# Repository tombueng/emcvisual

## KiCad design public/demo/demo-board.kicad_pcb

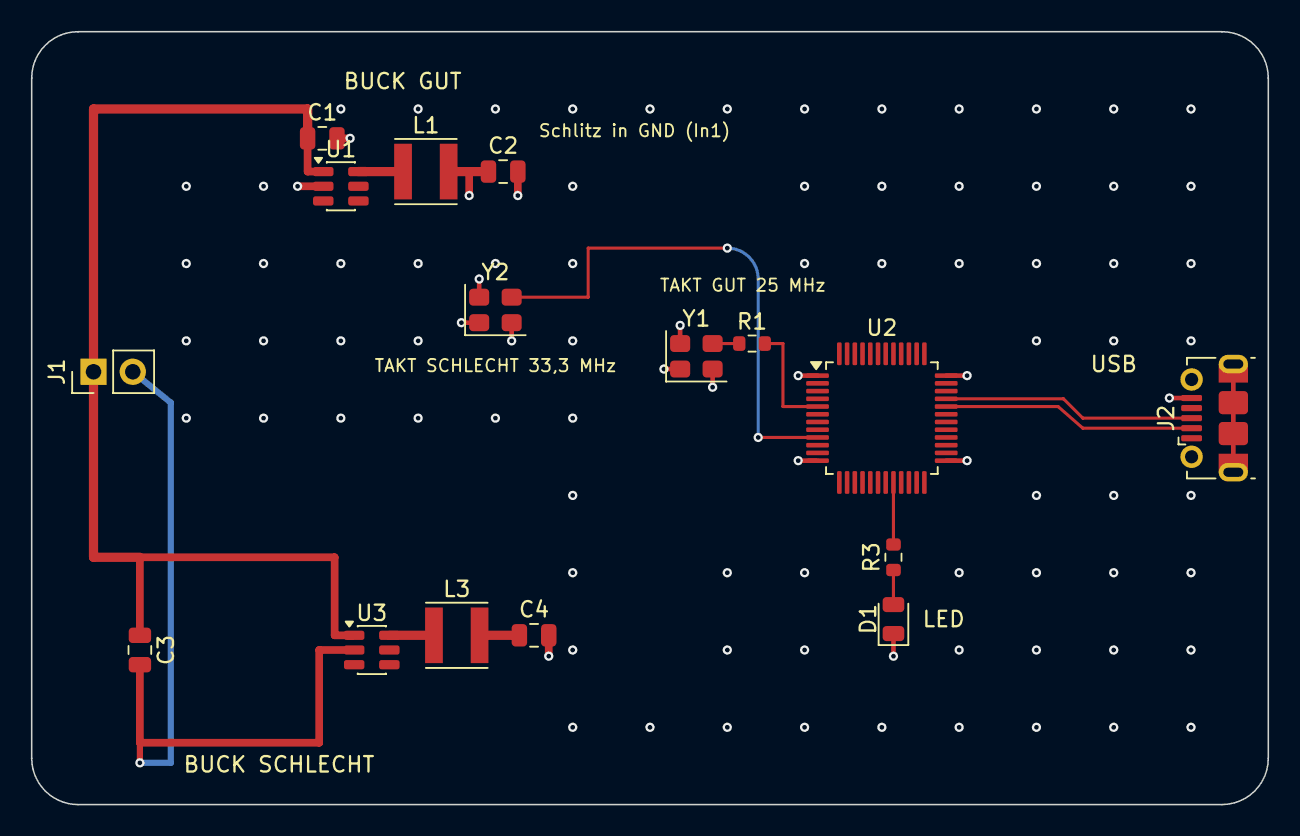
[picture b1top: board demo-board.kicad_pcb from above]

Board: 4 copper layers, 80.0 x 50.0 mm, 16 parts (0 on the bottom side), 13 nets.

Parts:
C1, C3: 10u; C_0805_2012Metric
C2, C4: 22u; C_0805_2012Metric
D1: LED; LED_0805_2012Metric
J1: VIN 12V; PinHeader_1x02_P2.54mm_Vertical
J2: USB; USB_Micro-B_Molex-105017-0001
L1, L3: 4u7; L_Vishay_IFSC-1515AH_4x4x1.8mm
R1: 33; R_0603_1608Metric
R3: 1k; R_0603_1608Metric
U1, U3: Buck 500 kHz (Demo); SOT-23-6
U2: MCU (Demo); LQFP-48_7x7mm_P0.5mm
Y1: 25 MHz; Oscillator_SMD_Abracon_ASE-4Pin_3.2x2.5mm
Y2: 33.333 MHz; Oscillator_SMD_Abracon_ASE-4Pin_3.2x2.5mm

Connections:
+1V8: C4.1, L3.2
+3V3: C2.1, L1.2, U2.1 (VDD), U2.36 (VDD), Y1.1 (OE), Y1.4 (VDD), Y2.1 (OE), Y2.4 (VDD)
CLK_BAD: U2.9 (CLK_IN2), Y2.3 (OUT)
CLK_GOOD: R1.2, U2.5 (OSC_IN)
CLK_GOOD_SRC: R1.1, Y1.3 (OUT)
GND: C1.2, C2.2, C3.2, C4.2, D1.1, J1.2 (GND), J2.5 (GND), J2.SH (SHIELD), U1.2 (GND), U2.12 (VSS), U2.25 (VSS), U3.2 (GND), Y1.2 (GND), Y2.2 (GND)
LED: R3.2, U2.20 (PB0)
LED_A: D1.2, R3.1
SW1: L1.1, U1.6 (SW)
SW3: L3.1, U3.6 (SW)
USB_DN: J2.2 (D-), U2.32 (USB_DN)
USB_DP: J2.3 (D+), U2.33 (USB_DP)
VIN: C1.1, C3.1, J1.1 (VIN), U1.1 (VIN), U3.1 (VIN)

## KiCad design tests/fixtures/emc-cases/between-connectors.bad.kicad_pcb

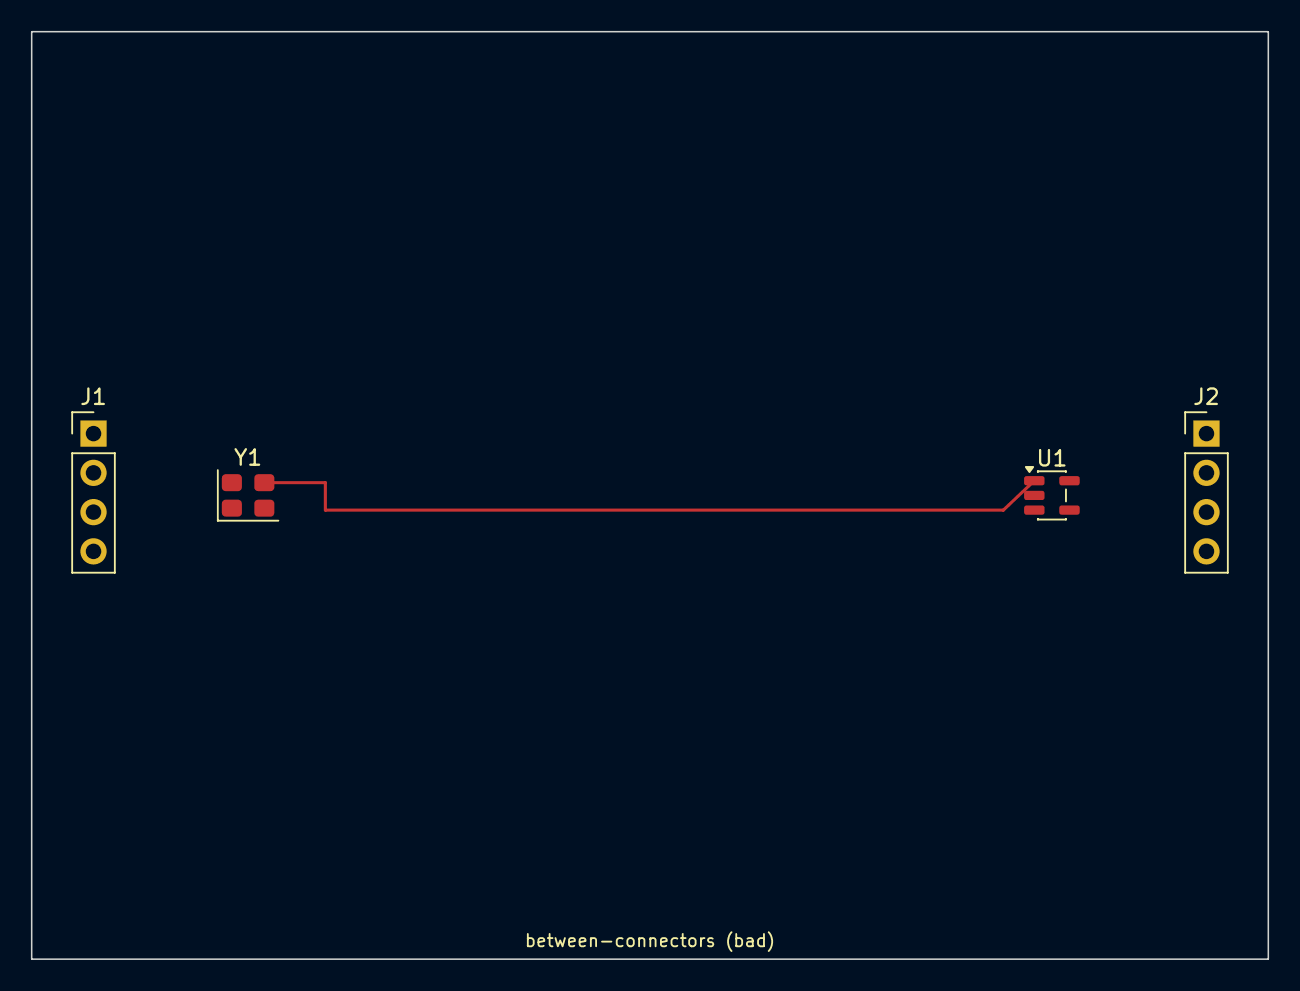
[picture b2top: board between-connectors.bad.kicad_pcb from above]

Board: 4 copper layers, 80.0 x 60.0 mm, 4 parts (0 on the bottom side), 5 nets.

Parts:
J1, J2: Kabel; PinHeader_1x04_P2.54mm_Vertical
U1: 74LVC1G04; SOT-23-5
Y1: 25MHz; Oscillator_SMD_Abracon_ASE-4Pin_3.2x2.5mm

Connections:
+3V3: U1.5, Y1.1, Y1.4
+5V: J1.1, J2.1
CLK: U1.1, Y1.3
D1: J1.3, J2.3
GND: J1.2, J1.4, J2.2, J2.4, U1.2, Y1.2
